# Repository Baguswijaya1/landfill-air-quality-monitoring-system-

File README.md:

# AQUOS - Air Quality Monitoring System

Repository ini adalah dokumentasi dan panduan penggunaan AQUOS (Air Quality Monitoring System), alat pemantau kualitas udara untuk area di sekitar tempat pembuangan sampah. Projek ini adalah Program Kerja KKN-PPM UGM di Desa Sumberrejo, Kecamatan Batur, Kabupaten Banjarnegara.

## ✨ Fitur Utama
- **Mendeteksi tiga jenis gas berbahaya** yang umum ditemui di tempat pembuangan sampah, seperti gas Metana (CH<sub>4</sub>), Amonia (NH<sub>3</sub>), dan Asam Sulfida (H<sub>2</sub>S).
- Pemantauan secara langsung lewat **LCD display** maupun melalui *smartphone* menggunakan **local dashboard**, sehingga bisa diakses di area sekitar alat.
- **Menggunakan sensor dan komponen biaya murah** (MQ2, MQ135, MQ135, ESP32).
- **Sistem yang dirancang modular**, memudahkan  penggantian sensor dan komponen apabila terjadi kerusakan.

## :exclamation:Disclaimer
- sensor gas dalam AQUOS memiliki tingkat kepekaan yang rendah, sehingga tidak dapat mendeteksi perbedaan kadar gas secara signifikan.
- hasil bacaan sensor hanya mewakili tingkat keberbahayaan gas berdasarkan sinyal dari sensor, bukan kadar gas yang sebenarnya dalam satuan yang akurat (ppm, %)

# :orange_book:Panduan Penggunaan Alat
### :battery: Menyalakan AQUOS
1. Hubungkan port USB tipe micro-B pada alat dengan sumber tenaga dengan tegangan 5V dan daya 25W. 
2. Anda bisa mentenagai alat menggunaakan adaptor charger smartphone 25W ke stop kontak rumah/gedung.
3. Alat akan aktif dan mulai mengambil data gas di lingkungan sekitar. 
4. Tunggu 30 menit untuk mendapat data sensor yang lebih akurat, karena sensor membutuhkan penyesuaian terlebih dahulu setelah dinyalakan

### :desktop_computer: Memantau kualitas udara lewat LCD
1. Hasil pengukuran tingkat kepekatan gas dapat dilihat langsung pada layar LCD.

### :signal_strength: Memantau Kualitas Udara Melalui *Smartphone*/Komputer dengan *Local Dashboard*
AQUOS tidak memerlukan akses internet untuk bisa dipantau lewat perangkat pribadi. Sebaliknya, alat ini berperan sebagai *access point*, dan data sensor dapat diakses dengan menghubungkan perangkat pribadi dengan koneksi alat dan masuk ke alamat IP alat lewat aplikasi *browser*. Berikut ini adalah langkah-langkahnya.
1. **Nyalakan alat**
2. **Siapkan perangkat pribadi** (smartphone/komputer) dan **hubungkan dengan jaringan yang disediakan oleh AQUOS**.
```
SSID = AQUOS-Batur
Password = batur123
```
SSID dan password dapat dikustomisasi dengan mengubah kode program di *aquos_code/include/access_point.h* 

4. **Buka aplikasi browser** lalu pergi ke alamat IP dari AQUOS dengan mengetik **192.168.4.1** pada panel penelusuran
5. Sekarang kamu bisa melihat kualitas udara saat ini. **Refresh halaman browser** untuk mendapatkan pembaruan data.

# Perawatan dan Pengembangan
## :hammer_and_wrench: Komponen Utama
| Nama Komponen | Fungsi | 
|:-------------------------|:----------------------:|
| ESP32 DevKit V1                    | Microcontroller sebagai Unit Pemroses Utama      |
| MQ2                      | Sensor Gas Metana (CH<sub>4</sub>)                          |
| MQ135                    | Sensor Gas Amonia (NH<sub>3</sub>)                          |
| MQ136                    | Sensor Gas Asam Sulfida (H<sub>2</sub>S)                    |
| LCD 16x2                 | Komponen untuk menampilkan bacaan sensor         |
| Modul TXS0108E           | Logic Level Shifter untuk konversi tegangan data keluar dan masuk ESP32|
</div>

## :construction: Struktur Projek

Projek ini terdiri dari tiga bagian utama:
* **aquos_code**: berisi kode program dari projek ini. Dibuat menggunakaan Arduino Framework dan PlatformIO.
* **aquos_pcb**: berisi desain PCB dari projek ini. Dapat dibuka menggunakan software KiCad 12.0.
* **aquos_chasing**: berisi desain chasing dari projek ini. Dibuat menggunakan Autodesk Inventor.

## :computer: Pengembangan
Projek ini adalah projek open-source. Anda bebas untuk menggunakan repository ini untuk projek Anda ataupun untuk pengembangan lebih lanjut.

```
git clone https://github.com/Baguswijaya1/landfill-air-quality-monitoring-system-.git
```
Untuk diskusi lebih lanjut, Anda dapat melakukan kontak dengan saya melalui email bagusanw@gmail.com

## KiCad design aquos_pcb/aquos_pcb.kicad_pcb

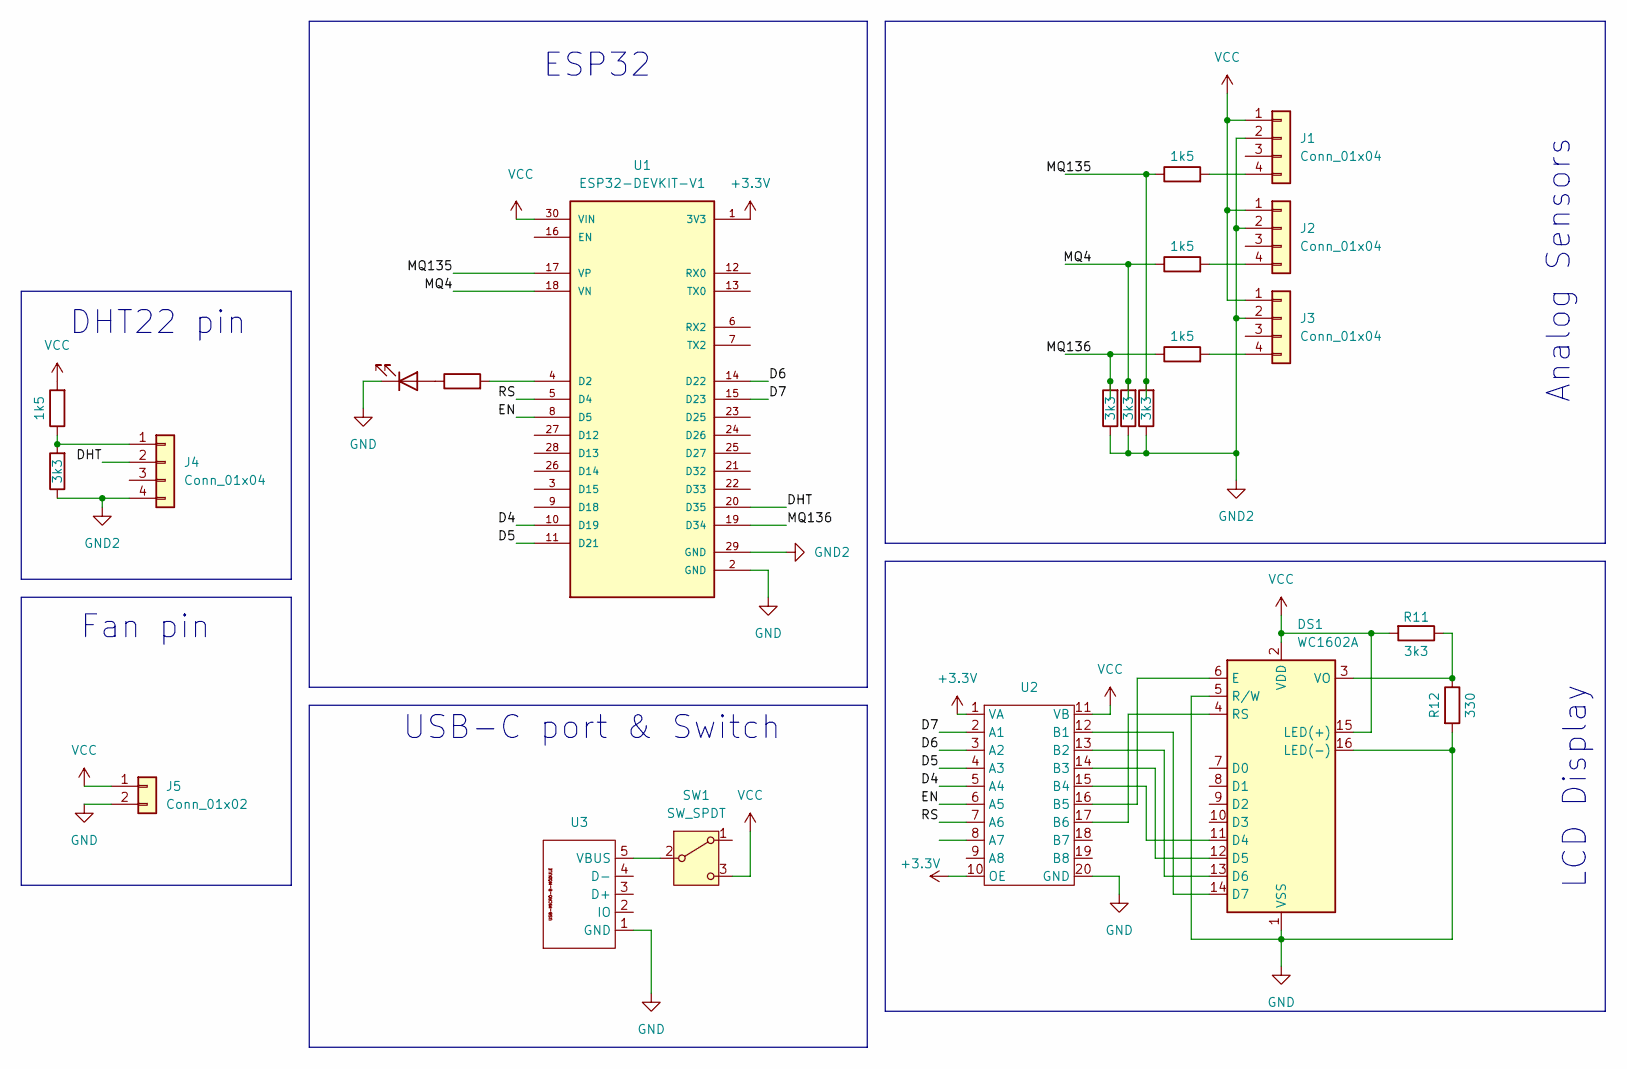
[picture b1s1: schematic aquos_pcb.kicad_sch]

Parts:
D1: LED; LED_D3.0mm_FlatTop
DS1: WC1602A
J1, J2, J3, J4: Conn_01x04; PinHeader_1x04_P2.54mm_Vertical
J5: Conn_01x02; PinHeader_1x02_P2.54mm_Vertical
R1: R; R_Axial_DIN0204_L3.6mm_D1.6mm_P5.08mm_Horizontal
R5, R6, R7, R13: 1k5; R_Axial_DIN0204_L3.6mm_D1.6mm_P5.08mm_Horizontal
R8, R9, R10, R11, R14: 3k3; R_Axial_DIN0204_L3.6mm_D1.6mm_P5.08mm_Horizontal
R12: 330; R_Axial_DIN0204_L3.6mm_D1.6mm_P5.08mm_Horizontal
SW1: SW_SPDT; SW_Slide-03_Wuerth-WS-SLTV_10x2.5x6.4_P2.54mm
U1: ESP32-DEVKIT-V1; MODULE_ESP32_DEVKIT_V1; PARTREV N/A
U2: TXE0108E; txs0108e module
U3: USB-MICRO-B-MODULE

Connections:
+3.3V: U1.1 (3V3), U2.1 (VA), U2.10 (OE)
/D4: U1.10 (D19), U2.5 (A4)
/D5: U1.11 (D21), U2.4 (A3)
/D6: U1.14 (D22), U2.3 (A2)
/D7: U1.15 (D23), U2.2 (A1)
/DHT: J4.2, U1.20 (D35)
/EN: U1.8 (D5), U2.6 (A5)
/MQ4: R6.1, R9.2, U1.18 (VN)
/MQ135: R5.1, R10.2, U1.17 (VP)
/MQ136: R7.1, R8.2, U1.19 (D34)
/RS: U1.5 (D4), U2.7 (A6)
GND: D1.1 (K), DS1.1 (VSS), DS1.5 (R/W), DS1.16 (LED(-)), J5.2, R12.2, U1.2 (GND), U2.20 (GND), U3.1 (GND)
GND2: J1.2, J2.2, J3.2, J4.4, R8.1, R9.1, R10.1, R14.1, U1.29 (GND)
unnamed: D1.2 (A), R1.1
unnamed: DS1.11 (D4), U2.15 (B4)
unnamed: DS1.12 (D5), U2.14 (B3)
unnamed: DS1.13 (D6), U2.13 (B2)
unnamed: DS1.14 (D7), U2.12 (B1)
unnamed: DS1.6 (E), U2.16 (B5)
unnamed: DS1.4 (RS), U2.17 (B6)
unnamed: DS1.3 (VO), R11.1, R12.1
unnamed: J1.4, R5.2
unnamed: J2.4, R6.2
unnamed: J3.4, R7.2
unnamed: J4.1, R13.1, R14.2
unnamed: SW1.2 (B), U3.5 (VBUS)
unnamed: R1.2, U1.4 (D2)
VCC: DS1.2 (VDD), DS1.15 (LED(+)), J1.1, J2.1, J3.1, J5.1, R11.2, R13.2, SW1.3 (C), U1.30 (VIN), U2.11 (VB)

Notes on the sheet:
LCD Display
USB-C port & Switch
ESP32
Fan pin
DHT22 pin
Analog Sensors

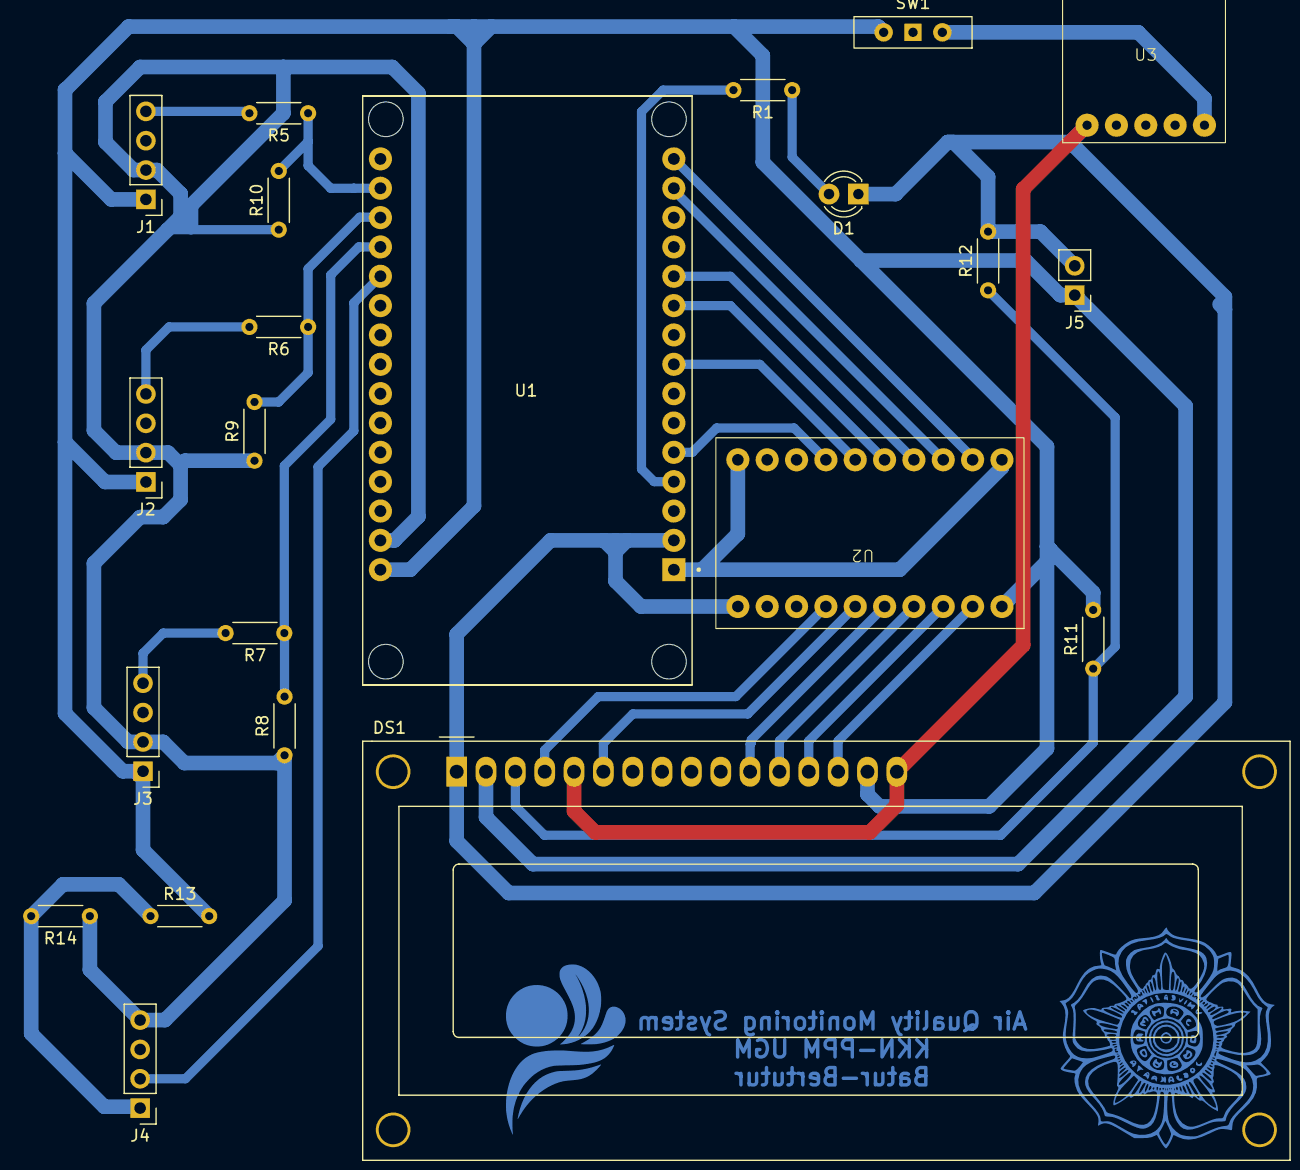
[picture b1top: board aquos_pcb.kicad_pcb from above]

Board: 2 copper layers, 22 parts (0 on the bottom side), 28 nets.

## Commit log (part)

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2026-06-05 add lcd display
2026-06-05 add .gitignore
2026-06-10 rearange lcd pin
2026-06-12 rearrange lcd pin
2026-06-12 load PCB design
2026-06-23 create AP and web dashboard
2026-06-25 add hazardous level to dashboard
2026-06-27 ready to print
2026-06-28 ready to push
